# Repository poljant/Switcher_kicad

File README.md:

# Switcher_kicad
Schematy do projektu Switcher

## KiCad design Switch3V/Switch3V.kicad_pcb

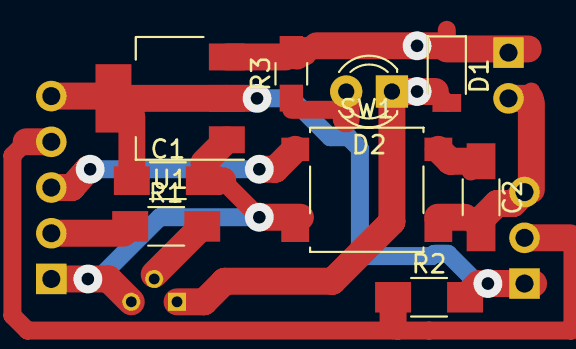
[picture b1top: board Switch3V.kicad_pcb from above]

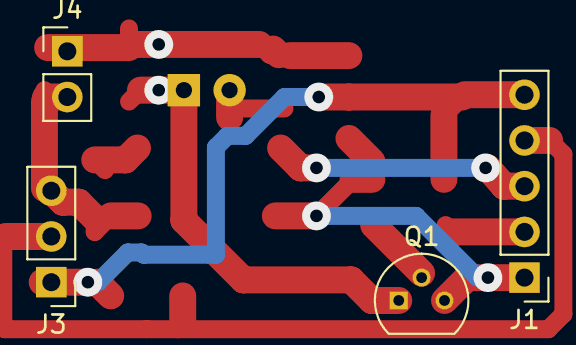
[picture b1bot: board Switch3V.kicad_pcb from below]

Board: 2 copper layers, 13 parts (4 on the bottom side), 9 nets.

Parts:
C1: 10uF; C_1206_HandSoldering
C2: 100nF; C_1206_HandSoldering
D1: D; D_1206
D2: LED; LED_D3.0mm
J1: ESP8266-12F; Pin_Header_Straight_1x05_Pitch2.54mm
J3: 1-Wire; Pin_Header_Straight_1x03_Pitch2.54mm
J4: 5V; Pin_Header_Straight_1x02_Pitch2.54mm
Q1: BC547; TO-92_Molded_Narrow
R1: 2k2; R_1206_HandSoldering
R2: 4k7; R_1206_HandSoldering
R3: 1k; R_0805_HandSoldering
SW1: SW_Push; SW_SPST_B3S-1000
U1: LM1117-3.3; SOT-223-3Lead_TabPin2

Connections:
+3V3: C1.1, J1.5, J3.1, R2.2, U1.2
+5V: D1.1, J4.1, R3.2, U1.3
GND: C1.2, C2.2, J1.1, J3.3, J4.2, Q1.3, SW1.2, U1.1
unnamed: C2.1, J1.3, SW1.1
unnamed: D1.2, D2.1, Q1.1
unnamed: D2.2, R3.1
unnamed: J1.2, R1.1
unnamed: J1.4, J3.2, R2.1
unnamed: Q1.2, R1.2

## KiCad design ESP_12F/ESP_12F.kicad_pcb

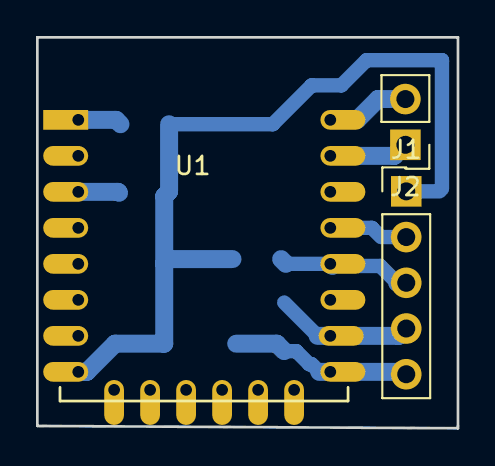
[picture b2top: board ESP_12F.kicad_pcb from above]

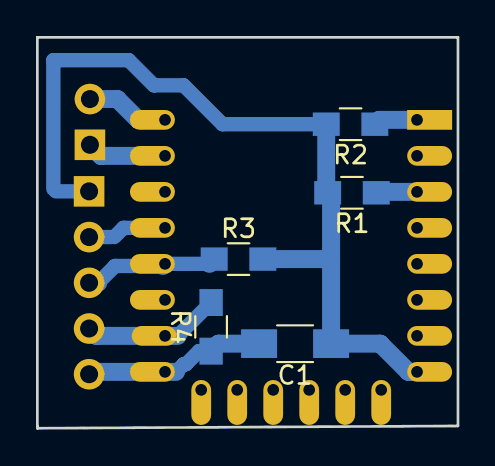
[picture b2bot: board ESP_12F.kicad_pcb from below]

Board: 2 copper layers, 23.4 x 21.7 mm, 8 parts (5 on the bottom side), 9 nets.

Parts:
C1: 100nF; C_1206_HandSoldering
J1: Conn1; Pin_Header_Straight_1x05_Pitch2.54mm
J2: TxRx; Pin_Header_Straight_1x02_Pitch2.54mm
R1, R2, R3, R4: 10k; R_0805_HandSoldering
U1: ESP8266_ESP-12E; ESP-12E

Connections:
+3V3: C1.1, J1.1, R1.2, R2.2, R3.2, U1.8
GND: C1.2, J1.5, R4.1, U1.9
unnamed: J1.2, U1.13
unnamed: J1.3, R3.1, U1.12
unnamed: J1.4, R4.2, U1.10
unnamed: R1.1, U1.3
unnamed: R2.1, U1.1
Rx: J2.1, U1.15
Tx: J2.2, U1.16

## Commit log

2019-12-09 didano pliki
2019-12-10 dodanie płytki ESP-12mikro
